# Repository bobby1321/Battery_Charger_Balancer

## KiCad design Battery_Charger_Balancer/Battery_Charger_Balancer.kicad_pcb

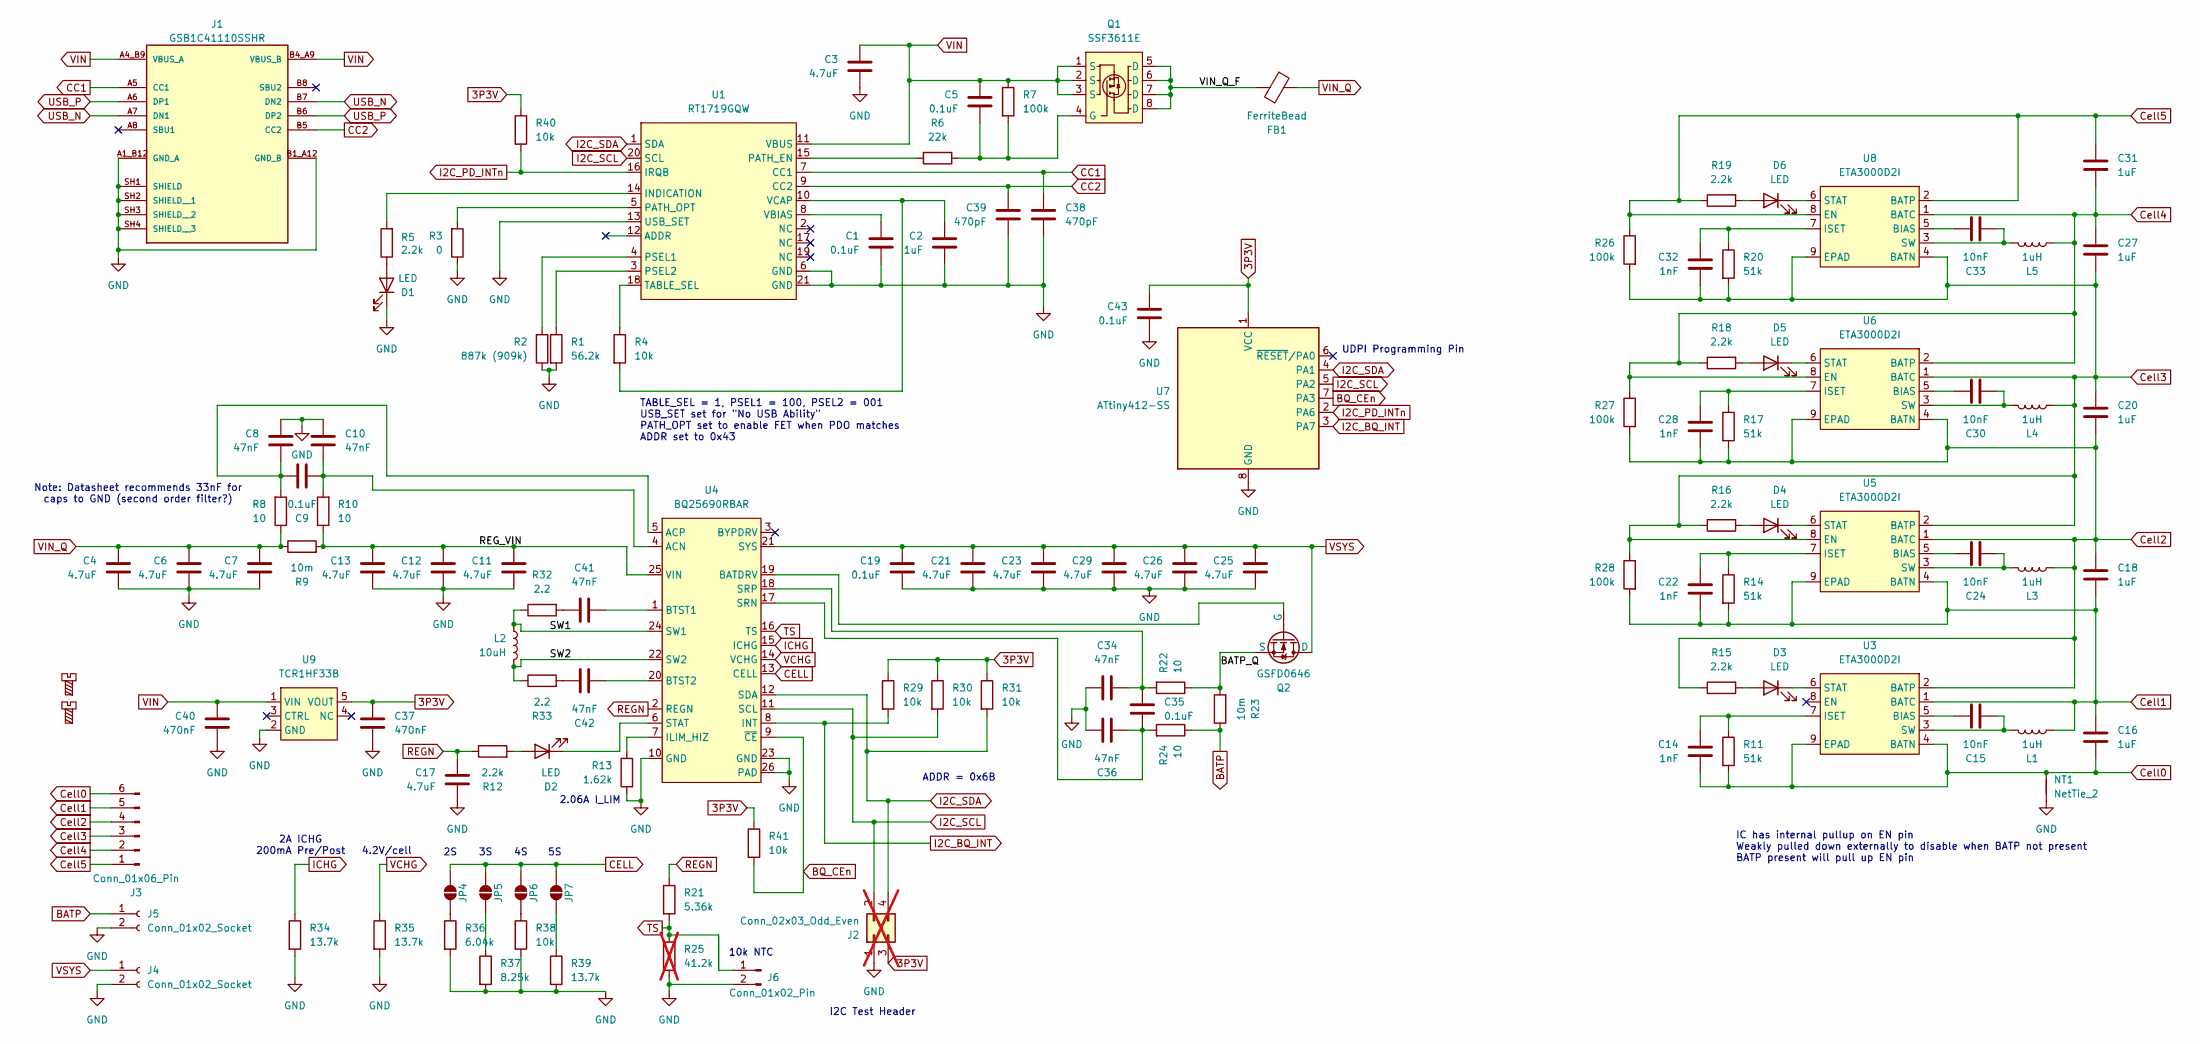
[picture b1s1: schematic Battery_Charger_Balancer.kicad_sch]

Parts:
C1, C5, C9, C19, C35, C43: 0.1uF; C_0603_1608Metric_Pad1.08x0.95mm_HandSolder
C2, C16, C18, C20, C27, C31: 1uF; C_0603_1608Metric_Pad1.08x0.95mm_HandSolder
C3, C4, C6, C7, C11, C12, C13, C17, C21, C23, C25, C26, C29: 4.7uF; C_0603_1608Metric_Pad1.08x0.95mm_HandSolder
C8, C10, C34, C36, C41, C42: 47nF; C_0603_1608Metric_Pad1.08x0.95mm_HandSolder
C14, C22, C28, C32: 1nF; C_0603_1608Metric_Pad1.08x0.95mm_HandSolder
C15, C24, C30, C33: 10nF; C_0603_1608Metric_Pad1.08x0.95mm_HandSolder
C37, C40: 470nF; C_0603_1608Metric_Pad1.08x0.95mm_HandSolder
C38, C39: 470pF; C_0603_1608Metric_Pad1.08x0.95mm_HandSolder
D1, D2, D3, D4, D5, D6: LED; LED_0603_1608Metric_Pad1.05x0.95mm_HandSolder
FB1: FerriteBead; L_0603_1608Metric_Pad1.05x0.95mm_HandSolder
H1, H2: MountingScrew; MountingHole_2.2mm_M2
J1: GSB1C41110SSHR; AMPHENOL_GSB1C41110SSHR; PARTREV AX1
J2: Conn_02x03_Odd_Even; PinHeader_2x02_P2.54mm_Vertical; not fitted
J3: Conn_01x06_Pin; JST_XH_B6B-XH-A_1x06_P2.50mm_Vertical
J4, J5: Conn_01x02_Socket; TerminalBlock_RND_205-00045_1x02_P5.00mm_Horizontal
J6: Conn_01x02_Pin; JST_XH_B2B-XH-A_1x02_P2.50mm_Vertical
JP4, JP5, JP6, JP7: SolderJumper_2_Open; Solder_Jumper_0603
L1, L3, L4, L5: 1uH; L_0805_2012Metric_Pad1.05x1.20mm_HandSolder
L2: 10uH; IND_PCC-M0748M-LE_PAN
NT1: NetTie_2; NetTie-2_SMD_Pad0.5mm
Q1: SSF3611E; SOIC-8_3.9x4.9mm_P1.27mm
Q2: GSFD0646; TO-252-2
R1: 56.2k; R_0603_1608Metric_Pad0.98x0.95mm_HandSolder
R2: 887k (909k); R_0603_1608Metric_Pad0.98x0.95mm_HandSolder
R3: 0; R_0603_1608Metric_Pad0.98x0.95mm_HandSolder
R4, R29, R30, R31, R38, R40, R41: 10k; R_0603_1608Metric_Pad0.98x0.95mm_HandSolder
R5, R12, R15, R16, R18, R19: 2.2k; R_0603_1608Metric_Pad0.98x0.95mm_HandSolder
R6: 22k; R_0603_1608Metric_Pad0.98x0.95mm_HandSolder
R7, R26, R27, R28: 100k; R_0603_1608Metric_Pad0.98x0.95mm_HandSolder
R8, R10, R22, R24: 10; R_0603_1608Metric_Pad0.98x0.95mm_HandSolder
R9, R23: 10m; R_1206_3216Metric_Pad1.30x1.75mm_HandSolder
R11, R14, R17, R20: 51k; R_0603_1608Metric_Pad0.98x0.95mm_HandSolder
R13: 1.62k; R_0603_1608Metric_Pad0.98x0.95mm_HandSolder
R21: 5.36k; R_0603_1608Metric_Pad0.98x0.95mm_HandSolder
R25: 41.2k; R_0603_1608Metric_Pad0.98x0.95mm_HandSolder; not fitted
R32, R33: 2.2; R_0603_1608Metric_Pad0.98x0.95mm_HandSolder
R34, R35, R39: 13.7k; R_0603_1608Metric_Pad0.98x0.95mm_HandSolder
R36: 6.04k; R_0603_1608Metric_Pad0.98x0.95mm_HandSolder
R37: 8.25k; R_0603_1608Metric_Pad0.98x0.95mm_HandSolder
U1: RT1719GQW; QFN-20-1EP_3.5x3.5mm_P0.5mm_EP2x2mm
U3, U5, U6, U8: ETA3000D2I; DFN-8-1EP_2x2mm_P0.5mm_EP0.6x1.2mm
U4: BQ25690RBAR; WQFN-26_L4.0-W3.5_BQ25690RBAR
U7: ATtiny412-SS; SOIC-8_3.9x4.9mm_P1.27mm
U9: TCR1HF33B; SC-74A-5_1.55x2.9mm_P0.95mm

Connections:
3P3V: C37.1, C43.1, J2.3, R29.1, R30.1, R31.1, R40.1, R41.1, U7.1 (VCC), U9.5 (VOUT)
/REG_VIN: C11.1, C12.1, C13.1, R9.2, R10.1, U4.25 (VIN)
/SW1: L2.2, R32.1, U4.24 (SW1)
/SW2: L2.1, R33.1, U4.22 (SW2)
/VIN_Q_F: FB1.2, Q1.5 (D), Q1.6 (D), Q1.7 (D), Q1.8 (D); also elsewhere on the board
BATP: J5.1, R23.1, R24.1
BQ_CEn: R41.2, U4.9 (~CE), U7.7 (PA3)
CC1: C38.1, J1.A5 (CC1), U1.7 (CC1)
CC2: C39.1, J1.B5 (CC2), U1.9 (CC2)
CELL: JP4.2 (B), JP5.2 (B), JP6.2 (B), JP7.2 (B), U4.13 (CELL)
Cell0: C14.2, C16.2, J3.6, NT1.2, R11.2, U3.4 (BATN), U3.9 (EPAD)
Cell1: C16.1, C18.2, C22.2, J3.5, L1.2, R14.2, R28.2, U3.1 (BATC), U5.4 (BATN), U5.9 (EPAD)
Cell2: C18.1, C20.2, C28.2, J3.4, L3.2, R15.1, R17.2, R27.2, U3.2 (BATP), U5.1 (BATC), U6.4 (BATN), U6.9 (EPAD)
Cell3: C20.1, C27.2, C32.2, J3.3, L4.2, R16.1, R20.2, R26.2, R28.1, U5.2 (BATP), U5.8 (EN), U6.1 (BATC), U8.4 (BATN), U8.9 (EPAD)
Cell4: C27.1, C31.2, J3.2, L5.2, R18.1, R27.1, U6.2 (BATP), U6.8 (EN), U8.1 (BATC)
Cell5: C31.1, J3.1, R19.1, R26.1, U8.2 (BATP), U8.8 (EN)
GND: C1.2, C2.2, C3.2, C4.2, C6.2, C7.2, C8.1, C10.1, C11.2, C12.2, C13.2, C17.2, C19.2, C21.2, C23.2, C25.2, C26.2, C29.2, C34.2, C36.2, C37.2, C38.2, C39.2, C40.2, C43.2, D1.1 (K), J1.A1_B12 (GND_A), J1.B1_A12 (GND_B), J1.SH1 (SHIELD), J1.SH2 (SHIELD__1), J1.SH3 (SHIELD__2), J1.SH4 (SHIELD__3), J2.1, J4.2, J5.2, J6.2, NT1.1, R1.2, R2.1, R3.1, R13.2, R25.2, R34.2, R35.2, R36.2, R37.2, R38.2, R39.2, U1.6 (GND), U1.13 (USB_SET), U1.21 (GND), U4.10 (GND), U4.23 (GND), U4.26 (PAD), U7.8 (GND), U9.2 (GND)
I2C_BQ_INT: R29.2, U4.8 (INT), U7.3 (PA7)
I2C_PD_INTn: R40.2, U1.16 (IRQB), U7.2 (PA6)
I2C_SCL: J2.2, R30.2, U1.20 (SCL), U4.11 (SCL), U7.5 (PA2)
I2C_SDA: J2.4, R31.2, U1.1 (SDA), U4.12 (SDA), U7.4 (PA1)
ICHG: R34.1, U4.15 (ICHG)
unnamed: C41.2, R32.2
unnamed: C42.2, R33.2
unnamed: D1.2 (A), R5.1
unnamed: D2.2 (A), R12.2
unnamed: D2.1 (K), U4.6 (STAT)
unnamed: D3.2 (A), R15.2
unnamed: D3.1 (K), U3.6 (STAT)
unnamed: D4.2 (A), R16.2
unnamed: D4.1 (K), U5.6 (STAT)
unnamed: D5.2 (A), R18.2
unnamed: D5.1 (K), U6.6 (STAT)
unnamed: D6.2 (A), R19.2
unnamed: D6.1 (K), U8.6 (STAT)
unnamed: JP4.1 (A), R36.1
unnamed: JP5.1 (A), R37.1
unnamed: JP6.1 (A), R38.1
unnamed: JP7.1 (A), R39.1
unnamed: R5.2, U1.14 (INDICATION)
unnamed: R6.2, U1.15 (PATH_EN)
unnamed: R3.2, U1.5 (PATH_OPT)
unnamed: R2.2, U1.4 (PSEL1)
unnamed: R1.1, U1.3 (PSEL2)
unnamed: R4.1, U1.18 (TABLE_SEL)
unnamed: C1.1, U1.8 (VBIAS)
unnamed: C2.1, R4.2, U1.10 (VCAP)
unnamed 47: C5.2, Q1.4 (G), R6.1, R7.2; also elsewhere on the board
unnamed: C15.2, U3.5 (BIAS)
unnamed: C14.1, R11.1, U3.7 (ISET)
unnamed: C15.1, L1.1, U3.3 (SW)
unnamed: C9.1, C10.2, R10.2, U4.4 (ACN)
unnamed: C8.2, C9.2, R8.2, U4.5 (ACP)
unnamed: C41.1, U4.1 (BTST1)
unnamed: C42.1, U4.20 (BTST2)
unnamed: R13.1, U4.7 (ILIM_HIZ)
unnamed: C35.2, C36.1, R24.2, U4.17 (SRN)
unnamed: C34.1, C35.1, R22.2, U4.18 (SRP)
unnamed: C24.2, U5.5 (BIAS)
unnamed: C22.1, R14.1, U5.7 (ISET)
unnamed: C24.1, L3.1, U5.3 (SW)
unnamed: C30.2, U6.5 (BIAS)
unnamed: C28.1, R17.1, U6.7 (ISET)
unnamed: C30.1, L4.1, U6.3 (SW)
unnamed: C33.2, U8.5 (BIAS)
unnamed: C32.1, R20.1, U8.7 (ISET)
unnamed: C33.1, L5.1, U8.3 (SW)
REGN: C17.1, R12.1, R21.1, U4.2 (REGN)
TS: J6.1, R21.2, R25.1, U4.16 (TS)
USB_N: J1.A7 (DN1), J1.B7 (DN2)
USB_P: J1.A6 (DP1), J1.B6 (DP2)
VCHG: R35.1, U4.14 (VCHG)
VIN_Q: C4.1, C6.1, C7.1, FB1.1, R8.1, R9.1

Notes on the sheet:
4.2V/cell
UDPI Programming Pin
2.06A I_LIM
Note: Datasheet recommends 33nF for caps to GND (second order filter?)
2A ICHG 200mA Pre/Post
10k NTC
I2C Test Header
ADDR = 0x6B
IC has internal pullup on EN pin Weakly pulled down externally to disable when BATP not present BATP present will pull up EN pin
TABLE_SEL = 1, PSEL1 = 100, PSEL2 = 001 USB_SET set for "No USB Ability" PATH_OPT set to enable FET when PDO matches ADDR set to 0x43

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
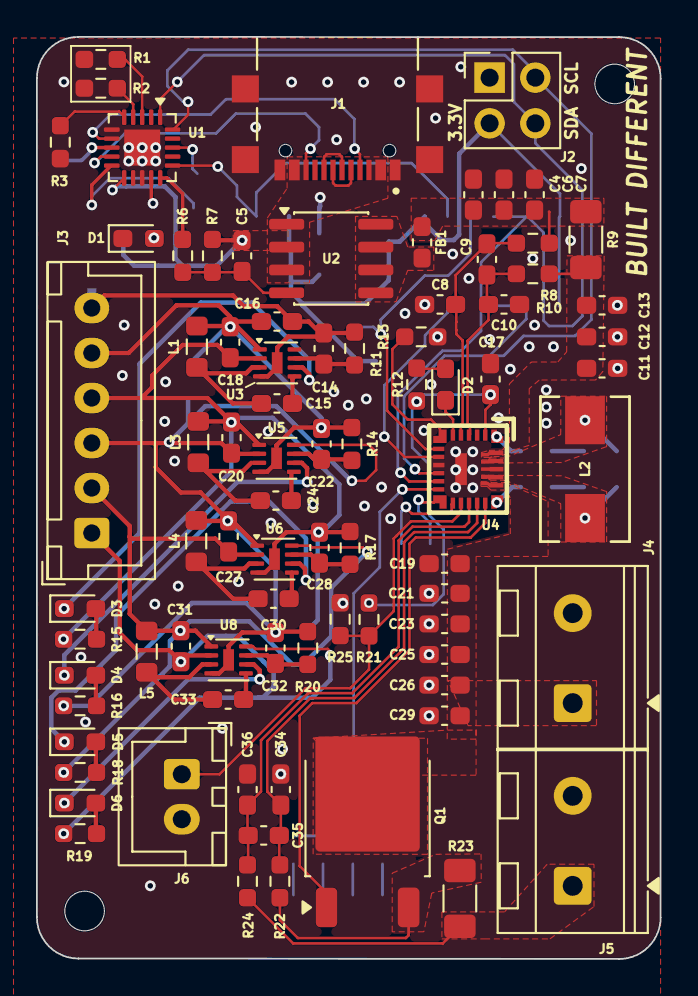
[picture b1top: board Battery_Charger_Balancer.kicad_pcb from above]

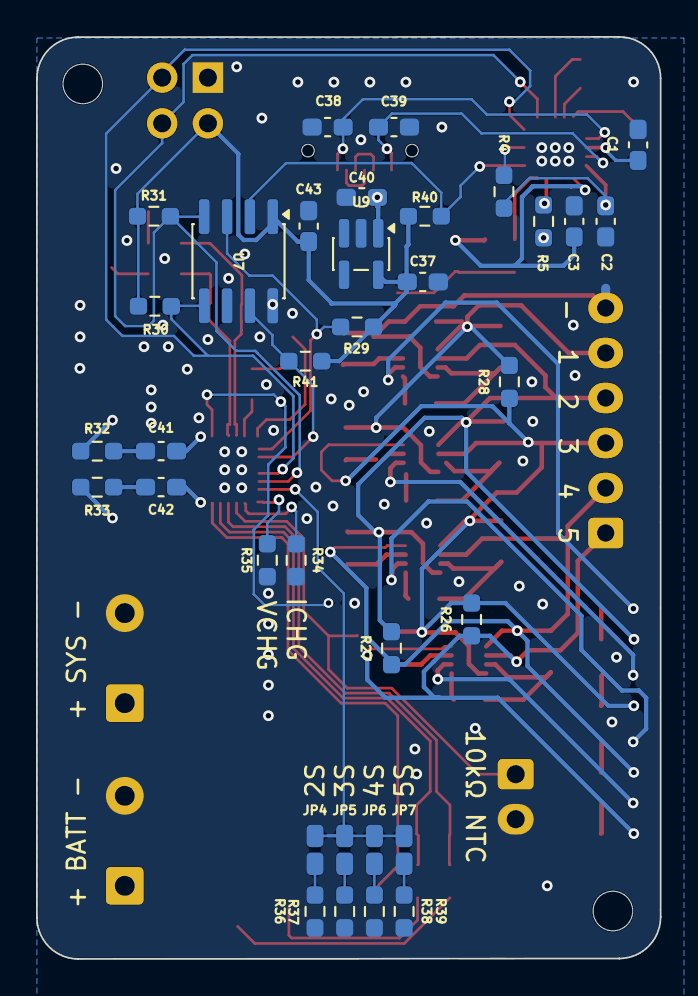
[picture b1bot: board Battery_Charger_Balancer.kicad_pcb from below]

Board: 2 copper layers, 34.6 x 51.2 mm, 119 parts (35 on the bottom side), 77 nets.

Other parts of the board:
U2: SSF3611E; SOIC-8_3.9x4.9mm_P1.27mm

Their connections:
/VIN_Q_F: U2.5 (D), U2.6 (D), U2.7 (D), U2.8 (D); also elsewhere on the board
unnamed 47: U2.4 (G); also elsewhere on the board

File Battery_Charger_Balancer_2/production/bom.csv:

Designator,Footprint,Quantity,Value,LCSC Part #
"C1, C19, C35, C5, C9",0603,5,0.1uF,
"C10, C34, C36, C41, C42, C8",0603,6,47nF,
"C11, C12, C13, C17, C21, C23, C25, C26, C29, C3, C4, C6, C7",0603,13,4.7uF,
"C14, C22, C28, C32",0603,4,1nF,
"C15, C24, C30, C33",0603,4,10nF,
"C16, C18, C20, C27, C31",0603,5,10uF,
C2,0603,1,1uF,
"C37, C40",0603,2,470nF,
"C38, C39",0603,2,470pF,
"D1, D2, D3, D4, D5, D6",0603,6,LED,
FB1,0603,1,FerriteBead,
J1,AMPHENOL_GSB1C41110SSHR,1,GSB1C41110SSHR,
J3,JST_XH_B6B-XH-A_1x06_P2.50mm_Vertical,1,Conn_01x06_Pin,
"J4, J5",TerminalBlock_RND_205-00045_1x02_P5.00mm_Horizontal,2,Conn_01x02_Socket,
J6,JST_XH_B2B-XH-A_1x02_P2.50mm_Vertical,1,Conn_01x02_Pin,
"L1, L3, L4, L5",0805,4,1uH,
L2,IND_ETQP5M100YFC,1,10uH,
Q1,TO-252-2,1,GSFD0646,
R1,0603,1,56.2k,
"R10, R22, R24, R8",0603,4,10,
"R11, R14, R17, R20",0603,4,51k,
"R12, R15, R16, R18, R19, R5",0603,6,2.2k,
"R13, R34, R35, R39",0603,4,13.7k,
R2,0603,1,453k,
R21,0603,1,5.36k,
"R23, R9",0603,2,10m,
R25,0603,1,41.2k,
"R26, R27, R28, R29, R30, R31, R4",0603,7,10k,
R3,0603,1,0,
"R32, R33",0603,2,2.2,
R36,0603,1,6.04k,
R37,0603,1,8.25k,
R38,0603,1,11k,
R6,0603,1,22k,
R7,0603,1,100k,
SW1,SW3_CSS-1210TB_NDC,1,SW_SPDT,
U1,QFN-20-1EP_3.5x3.5mm_P0.5mm_EP2x2mm,1,RT1719GQW,
U10,SOT-23-3,1,BAV74_215,
U2,SOIC-8_3.9x4.9mm_P1.27mm,1,SSF3611E,
"U3, U5, U6, U8",DFN-8-1EP_2x2mm_P0.5mm_EP0.6x1.2mm,4,ETA3000D2I,
U4,WQFN-26_L4.0-W3.5_BQ25690RBAR,1,BQ25690RBAR,
U9,SC-74A-5_1.55x2.9mm_P0.95mm,1,TCR1HF33B,

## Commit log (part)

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2026-05-10 Updates after production of first rev
2026-05-17 Finial version of the original design
